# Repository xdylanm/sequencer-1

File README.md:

# Sequencer One

An open step sequencer platform.

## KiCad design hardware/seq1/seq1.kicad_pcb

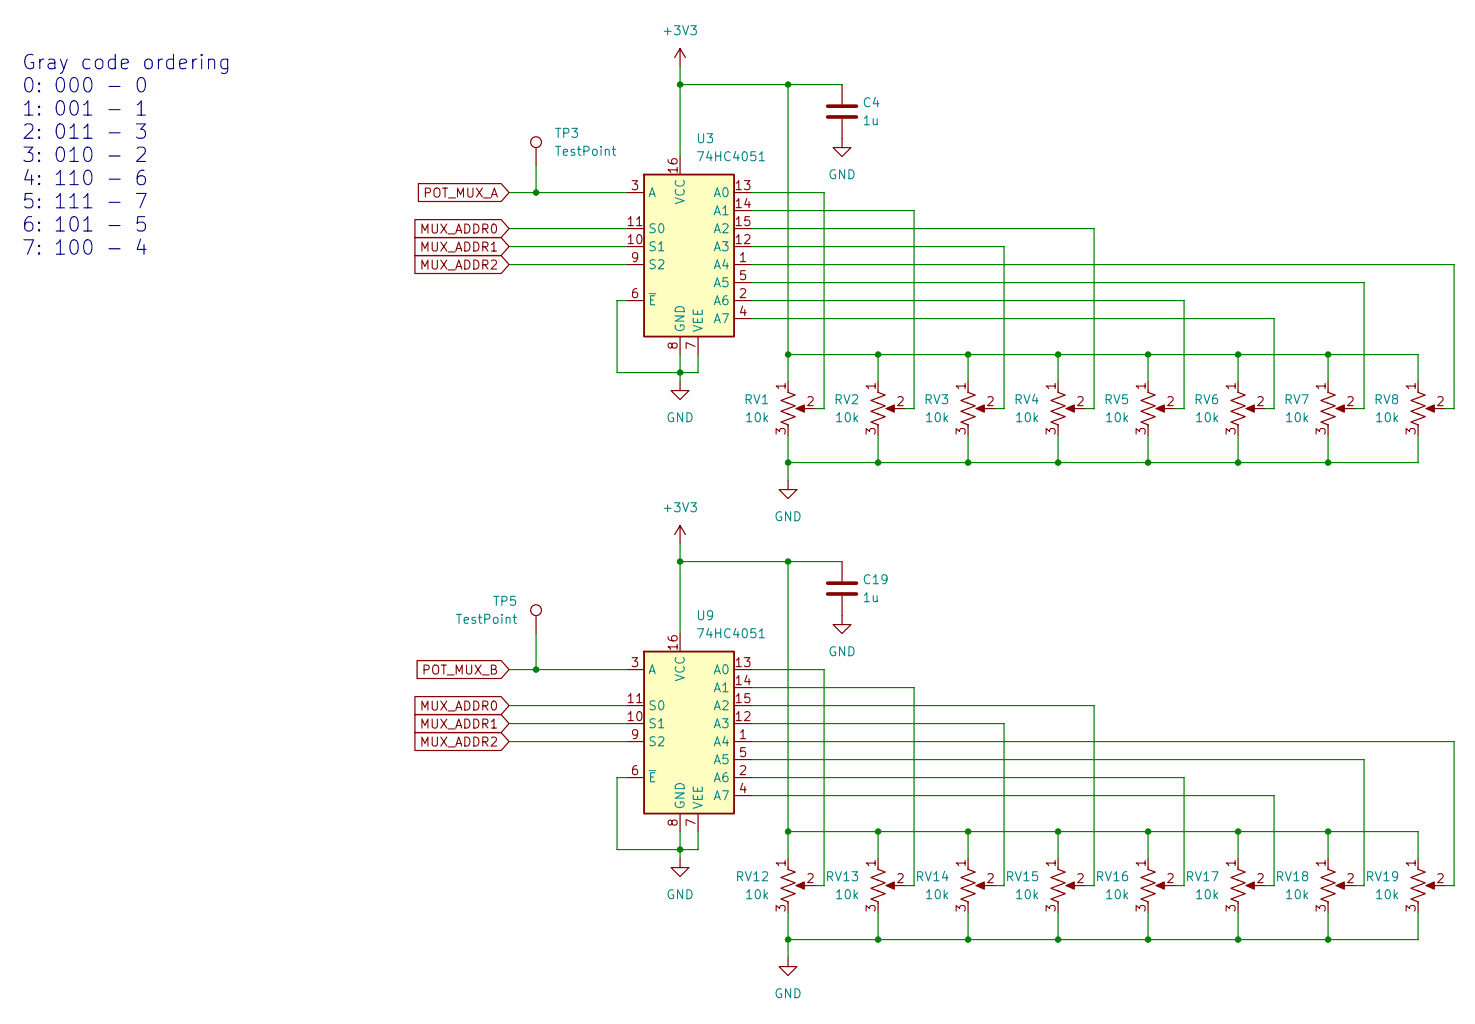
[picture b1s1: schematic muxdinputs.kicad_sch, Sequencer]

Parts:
C4, C19: 1u; C_Disc_D5.0mm_W2.5mm_P2.50mm
RV1, RV2, RV3, RV4, RV5, RV6, RV7, RV8, RV12, RV13, RV14, RV15, RV16, RV17, RV18, RV19: 10k; Potentiometer_Bourns_PTV09A-1_Single_Vertical
TP3, TP5: TestPoint; PinHeader_1x01_P2.54mm_Vertical
U3, U9: 74HC4051; DIP-16_W7.62mm_Socket

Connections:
+3V3: C4.1, C19.1, RV1.1, RV2.1, RV3.1, RV4.1, RV5.1, RV6.1, RV7.1, RV8.1, RV12.1, RV13.1, RV14.1, RV15.1, RV16.1, RV17.1, RV18.1, RV19.1, U3.16 (VCC), U9.16 (VCC); also elsewhere on the board
GND: C4.2, C19.2, RV1.3, RV2.3, RV3.3, RV4.3, RV5.3, RV6.3, RV7.3, RV8.3, RV12.3, RV13.3, RV14.3, RV15.3, RV16.3, RV17.3, RV18.3, RV19.3, U3.6 (~E), U3.7 (VEE), U3.8 (GND), U9.6 (~E), U9.7 (VEE), U9.8 (GND); also elsewhere on the board
MUX_ADDR0: U3.11 (S0), U9.11 (S0); also elsewhere on the board
MUX_ADDR1: U3.10 (S1), U9.10 (S1); also elsewhere on the board
MUX_ADDR2: U3.9 (S2), U9.9 (S2); also elsewhere on the board
unnamed: RV1.2, U3.13 (A0)
unnamed: RV2.2, U3.14 (A1)
unnamed: RV4.2, U3.15 (A2)
unnamed: RV3.2, U3.12 (A3)
unnamed: RV8.2, U3.1 (A4)
unnamed: RV7.2, U3.5 (A5)
unnamed: RV5.2, U3.2 (A6)
unnamed: RV6.2, U3.4 (A7)
unnamed: RV12.2, U9.13 (A0)
unnamed: RV13.2, U9.14 (A1)
unnamed: RV15.2, U9.15 (A2)
unnamed: RV14.2, U9.12 (A3)
unnamed: RV19.2, U9.1 (A4)
unnamed: RV18.2, U9.5 (A5)
unnamed: RV16.2, U9.2 (A6)
unnamed: RV17.2, U9.4 (A7)
POT_MUX_A: TP3.1, U3.3 (A); also elsewhere on the board
POT_MUX_B: TP5.1, U9.3 (A); also elsewhere on the board

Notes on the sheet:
Gray code ordering 0: 000 - 0 1: 001 - 1 2: 011 - 3 3: 010 - 2 4: 110 - 6 5: 111 - 7 6: 101 - 5 7: 100 - 4

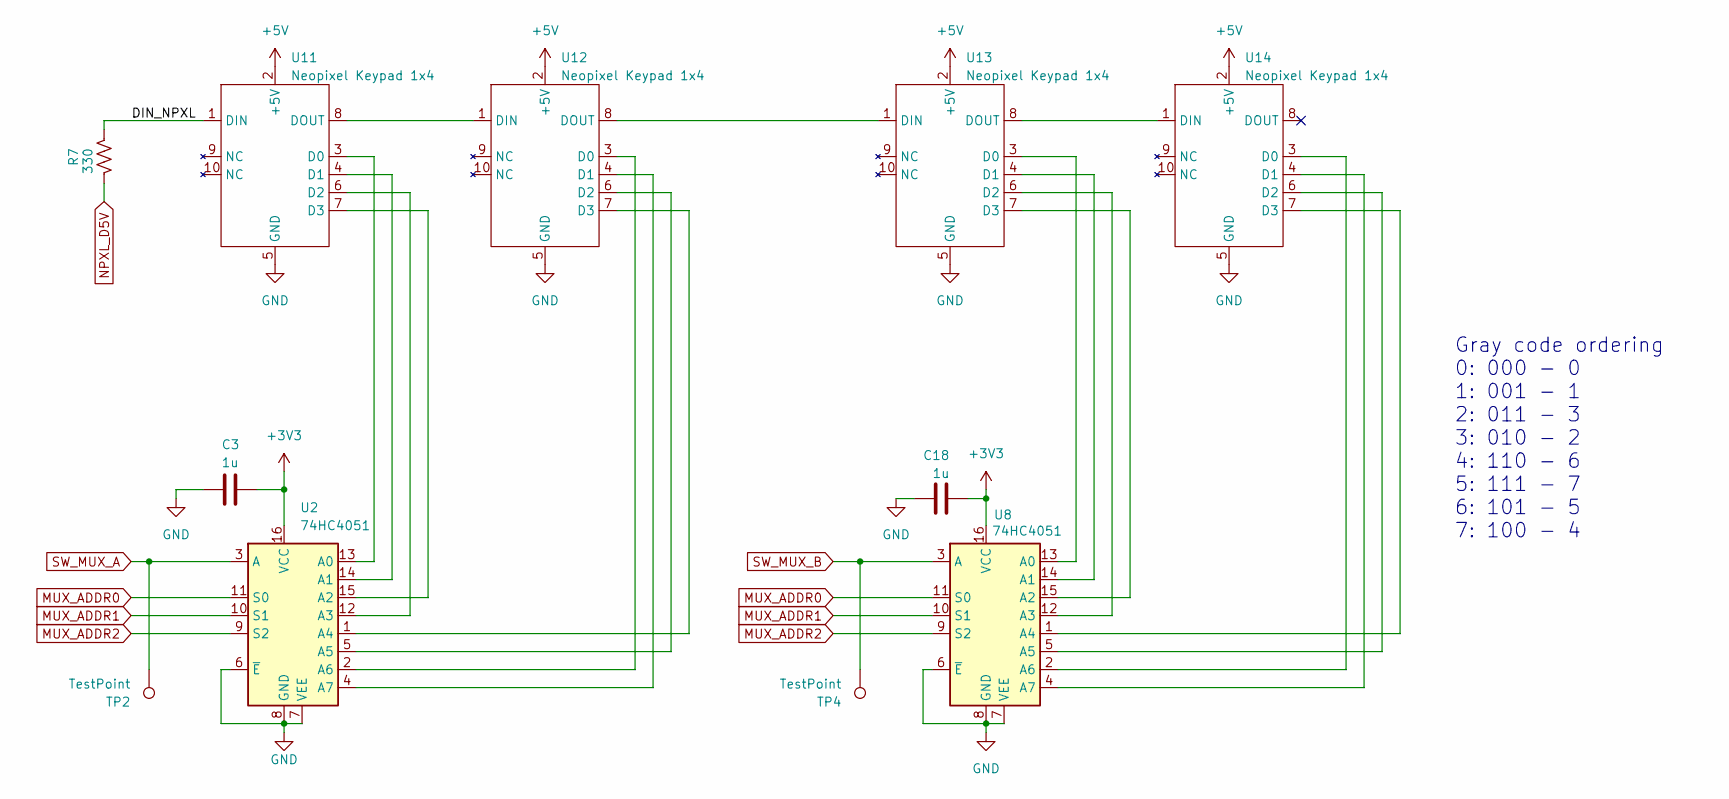
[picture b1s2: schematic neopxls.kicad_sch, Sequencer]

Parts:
C3, C18: 1u; C_Disc_D5.0mm_W2.5mm_P2.50mm
R7: 330; R_Axial_DIN0204_L3.6mm_D1.6mm_P2.54mm_Vertical
TP2, TP4: TestPoint; PinHeader_1x01_P2.54mm_Vertical
U2, U8: 74HC4051; DIP-16_W7.62mm_Socket
U11, U12, U13, U14: Neopixel Keypad 1x4; SW_Keypad_PushButton_1x4_Riser

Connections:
+3V3: C3.1, C18.2, U2.16 (VCC), U8.16 (VCC); also elsewhere on the board
+5V: U11.2 (+5V), U12.2 (+5V), U13.2 (+5V), U14.2 (+5V); also elsewhere on the board
/neopxls/DIN_NPXL: R7.2, U11.1 (DIN)
GND: C3.2, C18.1, U2.6 (~E), U2.7 (VEE), U2.8 (GND), U8.6 (~E), U8.7 (VEE), U8.8 (GND), U11.5 (GND), U12.5 (GND), U13.5 (GND), U14.5 (GND); also elsewhere on the board
MUX_ADDR0: U2.11 (S0), U8.11 (S0); also elsewhere on the board
MUX_ADDR1: U2.10 (S1), U8.10 (S1); also elsewhere on the board
MUX_ADDR2: U2.9 (S2), U8.9 (S2); also elsewhere on the board
NPXL_D5V: R7.1; also elsewhere on the board
unnamed: U2.13 (A0), U11.3 (D0)
unnamed: U2.14 (A1), U11.4 (D1)
unnamed: U2.12 (A3), U11.6 (D2)
unnamed: U2.15 (A2), U11.7 (D3)
unnamed: U11.8 (DOUT), U12.1 (DIN)
unnamed: U2.2 (A6), U12.3 (D0)
unnamed: U2.4 (A7), U12.4 (D1)
unnamed: U2.5 (A5), U12.6 (D2)
unnamed: U2.1 (A4), U12.7 (D3)
unnamed: U12.8 (DOUT), U13.1 (DIN)
unnamed: U8.13 (A0), U13.3 (D0)
unnamed: U8.14 (A1), U13.4 (D1)
unnamed: U8.12 (A3), U13.6 (D2)
unnamed: U8.15 (A2), U13.7 (D3)
unnamed: U13.8 (DOUT), U14.1 (DIN)
unnamed: U8.2 (A6), U14.3 (D0)
unnamed: U8.4 (A7), U14.4 (D1)
unnamed: U8.5 (A5), U14.6 (D2)
unnamed: U8.1 (A4), U14.7 (D3)
SW_MUX_A: TP2.1, U2.3 (A); also elsewhere on the board
SW_MUX_B: TP4.1, U8.3 (A); also elsewhere on the board

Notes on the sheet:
Gray code ordering 0: 000 - 0 1: 001 - 1 2: 011 - 3 3: 010 - 2 4: 110 - 6 5: 111 - 7 6: 101 - 5 7: 100 - 4

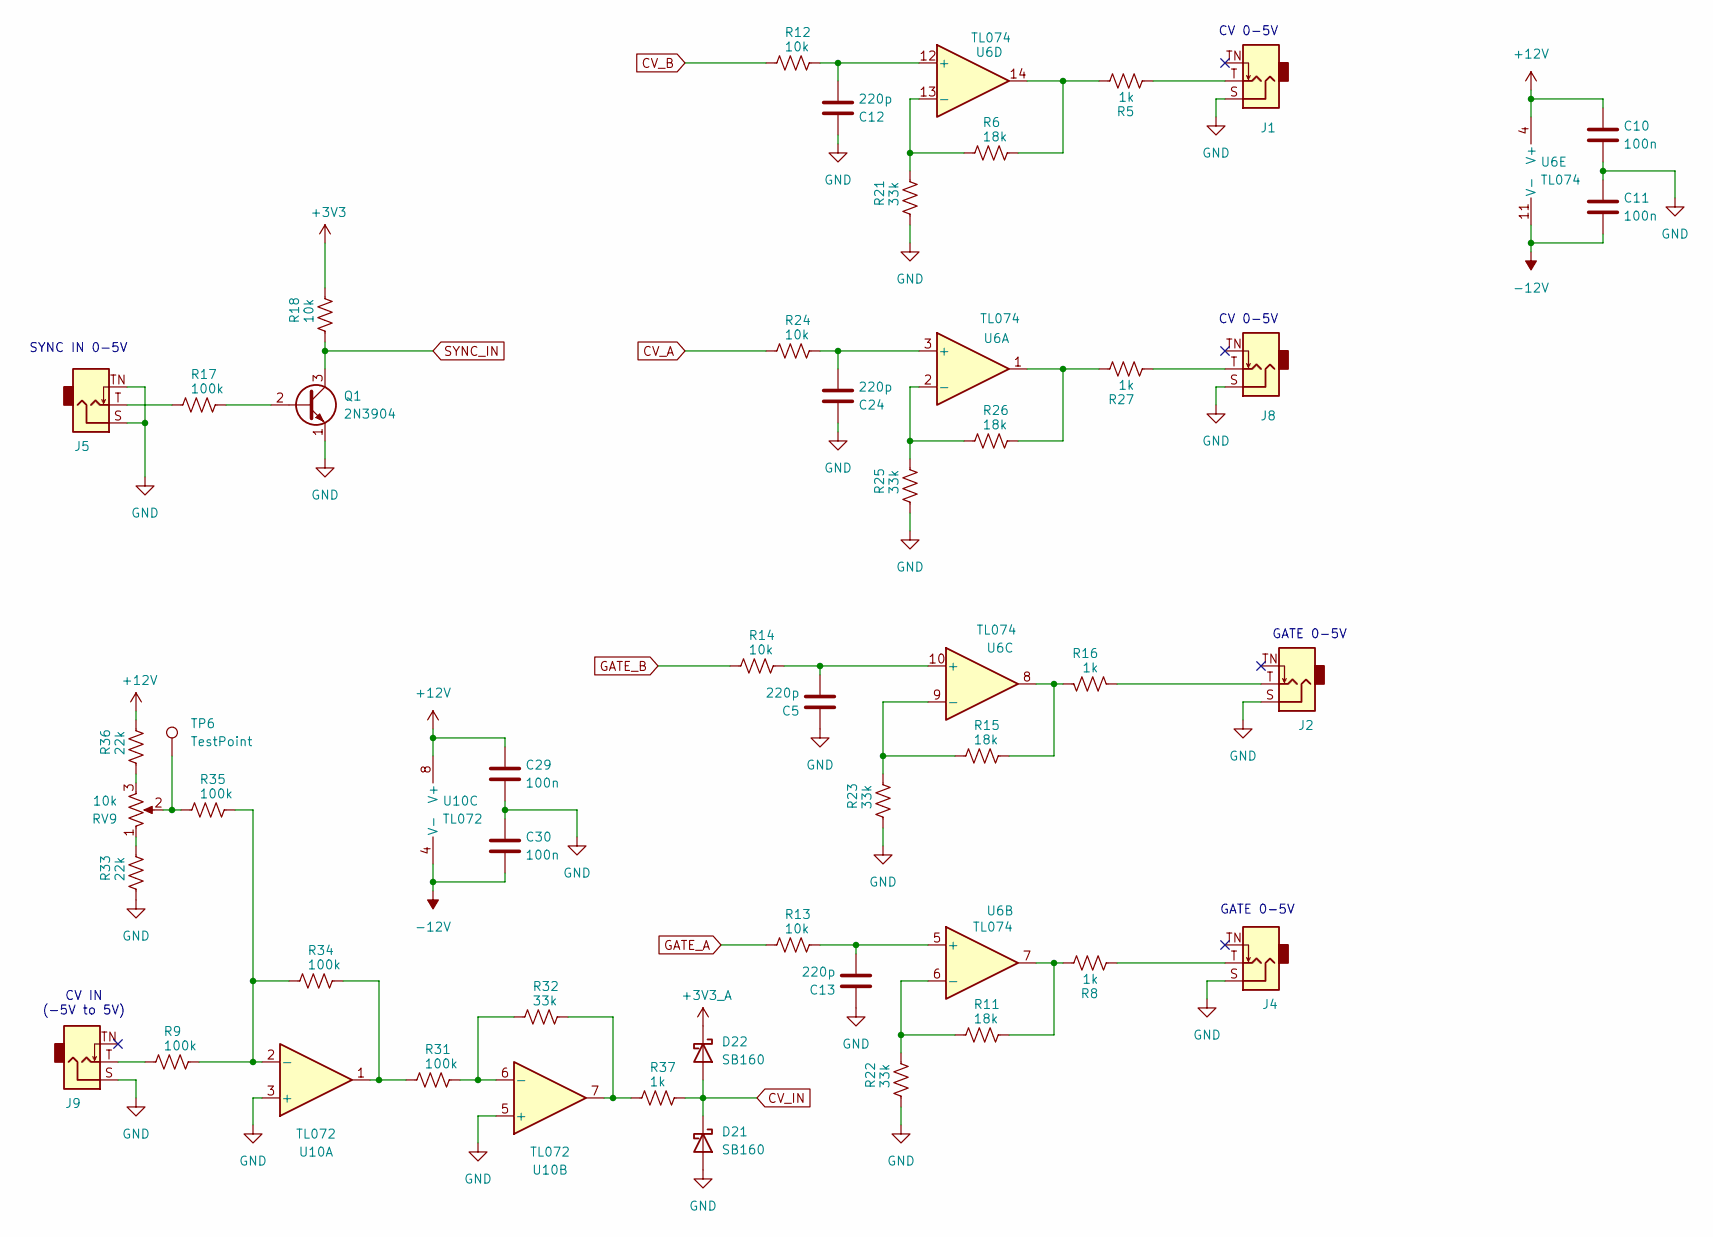
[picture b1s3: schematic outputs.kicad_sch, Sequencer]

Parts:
C5, C12, C13, C24: 220p; C_Disc_D5.0mm_W2.5mm_P2.50mm
C10, C11, C29, C30: 100n; C_Disc_D5.0mm_W2.5mm_P2.50mm
D21, D22: SB160; D_DO-35_SOD27_P2.54mm_Vertical_AnodeUp
J1, J2, J4, J5, J8, J9: AudioJack2_SwitchT; Jack_3.5mm_QingPu_WQP-PJ301M-12_Vertical
Q1: 2N3904; TO-92_Inline_Wide
R5, R8, R16, R37: 1k; R_Axial_DIN0204_L3.6mm_D1.6mm_P2.54mm_Vertical
R6, R11, R15, R26: 18k; R_Axial_DIN0204_L3.6mm_D1.6mm_P2.54mm_Vertical
R9, R17, R34, R35: 100k; R_Axial_DIN0204_L3.6mm_D1.6mm_P2.54mm_Vertical
R12, R18, R24: 10k; R_Axial_DIN0204_L3.6mm_D1.6mm_P2.54mm_Vertical
R13, R14: 10k; R_Axial_DIN0207_L6.3mm_D2.5mm_P10.16mm_Horizontal
R21, R22, R23, R25, R32: 33k; R_Axial_DIN0204_L3.6mm_D1.6mm_P2.54mm_Vertical
R27: 1k; R_Axial_DIN0204_L3.6mm_D1.6mm_P7.62mm_Horizontal
R31: 100k; R_Axial_DIN0204_L3.6mm_D1.6mm_P7.62mm_Horizontal
R33, R36: 22k; R_Axial_DIN0204_L3.6mm_D1.6mm_P2.54mm_Vertical
RV9: 10k; Potentiometer_Piher_PT-6-V_Vertical
TP6: TestPoint; PinHeader_1x01_P2.54mm_Vertical
U6: TL074; DIP-14_W7.62mm_Socket
U10: TL072; DIP-8_W7.62mm_Socket

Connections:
+3V3: R18.1; also elsewhere on the board
+3V3_A: D22.1 (K); also elsewhere on the board
+12V: C10.1, C29.1, R36.1, U6.4 (V+), U10.8 (V+); also elsewhere on the board
-12V: C11.2, C30.2, U6.11 (V-), U10.4 (V-); also elsewhere on the board
CV_A: R24.2; also elsewhere on the board
CV_B: R12.2; also elsewhere on the board
CV_IN: D21.1 (K), D22.2 (A), R37.1; also elsewhere on the board
GATE_A: R13.2; also elsewhere on the board
GATE_B: R14.2; also elsewhere on the board
GND: C5.1, C10.2, C11.1, C12.1, C13.1, C24.1, C29.2, C30.1, D21.2 (A), J1.S, J2.S, J4.S, J5.S, J5.TN, J8.S, J9.S, Q1.1 (E), R21.2, R22.2, R23.2, R25.2, R33.2, U10.3 (+), U10.5 (+); also elsewhere on the board
unnamed: J1.T, R5.2
unnamed: J2.T, R16.2
unnamed: J4.T, R8.2
unnamed: J5.T, R17.2
unnamed: J8.T, R27.2
unnamed: J9.T, R9.2
unnamed: Q1.2 (B), R17.1
unnamed: R5.1, R6.1, U6.14
unnamed: R8.1, R11.1, U6.7
unnamed: R15.1, R16.1, U6.8
unnamed: R26.1, R27.1, U6.1
unnamed: R31.2, R34.1, U10.1
unnamed: R32.1, R37.2, U10.7
unnamed: R33.1, RV9.1
unnamed: R35.2, RV9.2, TP6.1
unnamed: R36.2, RV9.3
unnamed: C24.2, R24.1, U6.3 (+)
unnamed: R25.1, R26.2, U6.2 (-)
unnamed: C13.2, R13.1, U6.5 (+)
unnamed: R11.2, R22.1, U6.6 (-)
unnamed: C5.2, R14.1, U6.10 (+)
unnamed: R15.2, R23.1, U6.9 (-)
unnamed: C12.2, R12.1, U6.12 (+)
unnamed: R6.2, R21.1, U6.13 (-)
unnamed: R9.1, R34.2, R35.1, U10.2 (-)
unnamed: R31.1, R32.2, U10.6 (-)
SYNC_IN: Q1.3 (C), R18.2; also elsewhere on the board

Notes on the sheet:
SYNC IN 0-5V
CV IN (-5V to 5V)
GATE 0-5V
CV 0-5V

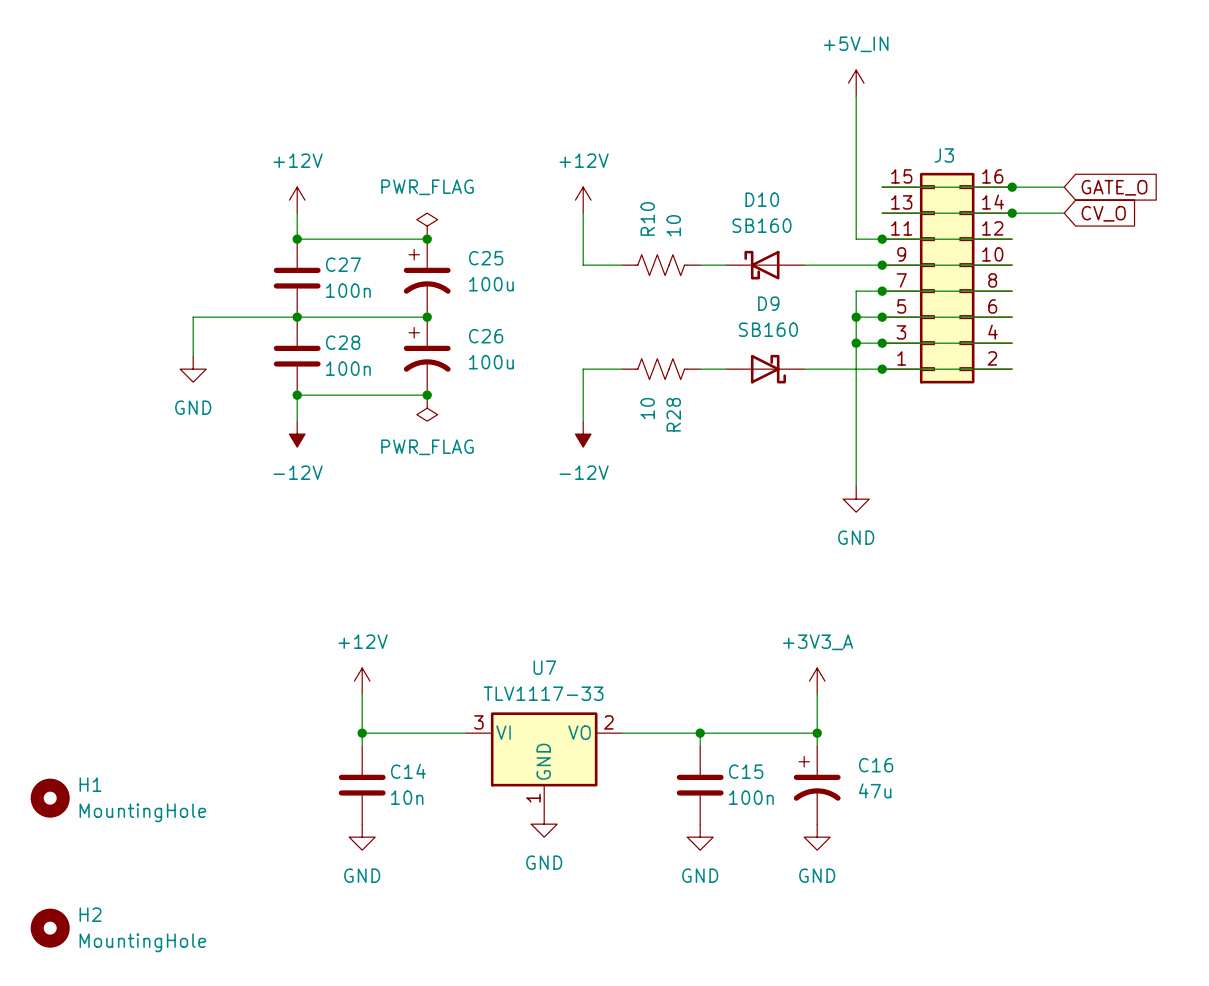
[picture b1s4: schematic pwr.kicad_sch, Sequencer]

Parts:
C14: 10n; C_Disc_D5.0mm_W2.5mm_P2.50mm
C15, C27, C28: 100n; C_Disc_D5.0mm_W2.5mm_P2.50mm
C16: 47u; CP_Radial_D5.0mm_P2.50mm
C25, C26: 100u; CP_Radial_D6.3mm_P2.50mm
D9, D10: SB160; D_DO-35_SOD27_P2.54mm_Vertical_AnodeUp
H1, H2: MountingHole; MountingHole_3.2mm_M3_DIN965
J3: Conn_02x08_Odd_Even; IDC-Header_2x08_P2.54mm_Vertical
R10: 10; R_Axial_DIN0204_L3.6mm_D1.6mm_P2.54mm_Vertical
R28: 10; R_Axial_DIN0207_L6.3mm_D2.5mm_P7.62mm_Horizontal
U7: TLV1117-33; SOT-223-3_TabPin2

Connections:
+3V3_A: C15.1, C16.1, U7.2 (VO); also elsewhere on the board
+5V_IN: J3.11, J3.12; also elsewhere on the board
+12V: C14.1, C25.1, C27.1, R10.1, U7.3 (VI); also elsewhere on the board
-12V: C26.2, C28.2, R28.2; also elsewhere on the board
CV_O: J3.13, J3.14
GATE_O: J3.15, J3.16
GND: C14.2, C15.2, C16.2, C25.2, C26.1, C27.2, C28.1, J3.3, J3.4, J3.5, J3.6, J3.7, J3.8, U7.1 (GND); also elsewhere on the board
unnamed: D9.2 (A), R28.1
unnamed: D9.1 (K), J3.1, J3.2
unnamed: D10.2 (A), J3.9, J3.10
unnamed: D10.1 (K), R10.2

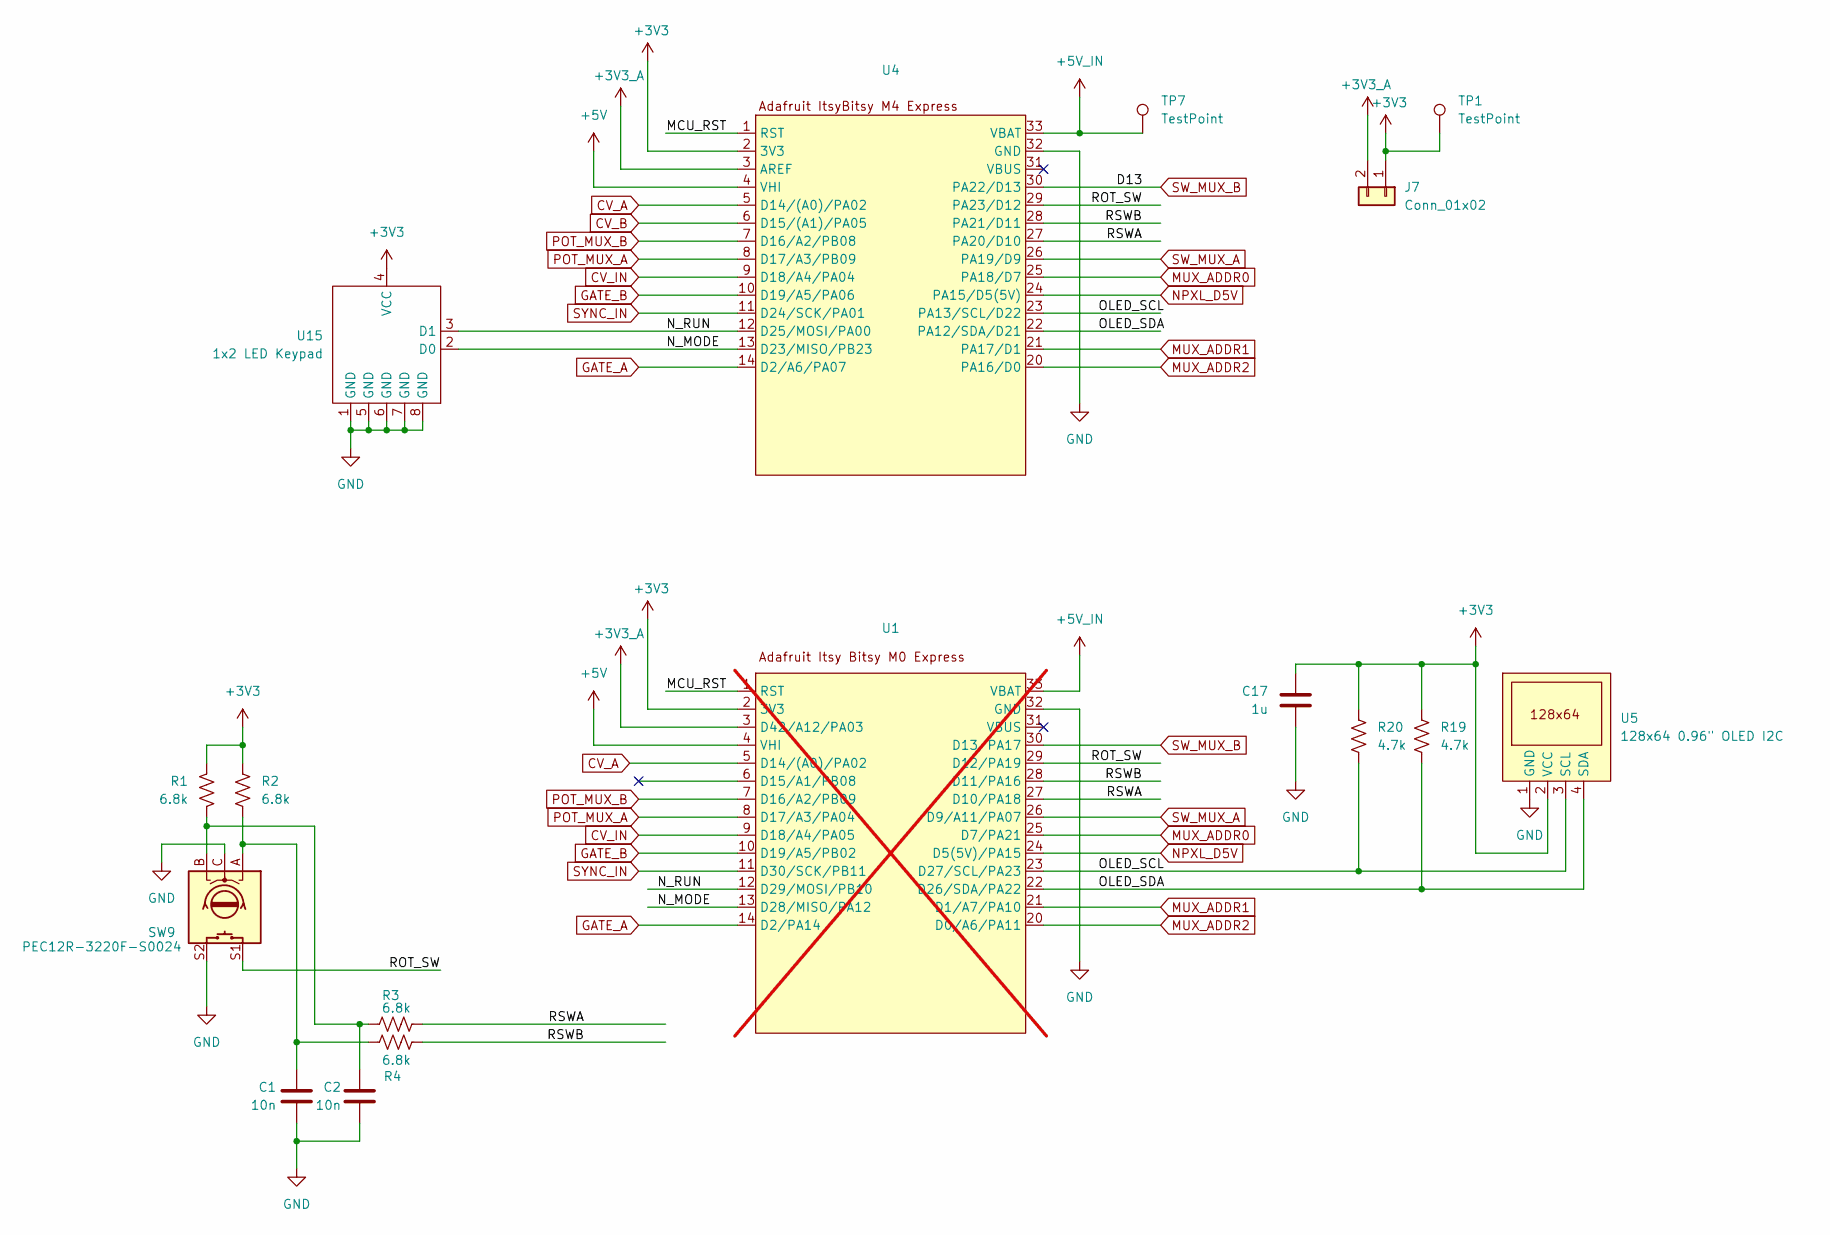
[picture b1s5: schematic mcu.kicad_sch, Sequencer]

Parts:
C1, C2: 10n; C_Disc_D5.0mm_W2.5mm_P2.50mm
C17: 1u; C_Disc_D5.0mm_W2.5mm_P2.50mm
J7: Conn_01x02; PinHeader_1x02_P2.54mm_Vertical
R1, R2, R3, R4: 6.8k; R_Axial_DIN0204_L3.6mm_D1.6mm_P2.54mm_Vertical
R19, R20: 4.7k; R_Axial_DIN0204_L3.6mm_D1.6mm_P2.54mm_Vertical
SW9: PEC12R-3220F-S0024; RotaryEncoder_Bourns_Vertical_PEC12R-3x17F-Sxxxx
TP1, TP7: TestPoint; PinHeader_1x01_P2.54mm_Vertical
U1: Adafruit_ItsyBitsy_M0_Express_DIP; not fitted
U4: Adafruit_ItsyBitsy_M0_Express_DIP
U5: 128x64 0.96" OLED I2C; OLED_0.96in_SSD1306_I2C
U15: 1x2 LED Keypad; SW_Keypad_PushButton_1x2_Riser

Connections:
+3V3: C17.1, J7.1, R1.1, R2.1, R19.1, R20.1, TP1.1, U1.2 (3V3), U4.2 (3V3), U5.2 (VCC), U15.4 (VCC); also elsewhere on the board
+3V3_A: J7.2, U1.3 (D42/A12/PA03), U4.3 (AREF); also elsewhere on the board
+5V: U1.4 (VHI), U4.4 (VHI); also elsewhere on the board
+5V_IN: TP7.1, U1.33 (VBAT), U4.33 (VBAT); also elsewhere on the board
/mcu/MCU_RST: U1.1 (RST), U4.1 (RST)
/mcu/N_MODE: U1.13 (D28/MISO/PA12), U4.13 (D23/MISO/PB23), U15.2 (D0)
/mcu/N_RUN: U1.12 (D29/MOSI/PB10), U4.12 (D25/MOSI/PA00), U15.3 (D1)
/mcu/OLED_SCL: R20.2, U1.23 (D27/SCL/PA23), U4.23 (PA13/SCL/D22), U5.3 (SCL)
/mcu/OLED_SDA: R19.2, U1.22 (D26/SDA/PA22), U4.22 (PA12/SDA/D21), U5.4 (SDA)
/mcu/ROT_SW: SW9.S1, U1.29 (D12/PA19), U4.29 (PA23/D12)
/mcu/RSWA: R3.1, U1.27 (D10/PA18), U4.27 (PA20/D10)
/mcu/RSWB: R4.1, U1.28 (D11/PA16), U4.28 (PA21/D11)
CV_A: U1.5 (D14/(A0)/PA02), U4.5 (D14/(A0)/PA02); also elsewhere on the board
CV_B: U4.6 (D15/(A1)/PA05); also elsewhere on the board
CV_IN: U1.9 (D18/A4/PA05), U4.9 (D18/A4/PA04); also elsewhere on the board
GATE_A: U1.14 (D2/PA14), U4.14 (D2/A6/PA07); also elsewhere on the board
GATE_B: U1.10 (D19/A5/PB02), U4.10 (D19/A5/PA06); also elsewhere on the board
GND: C1.2, C2.2, C17.2, SW9.C, SW9.S2, U1.32 (GND), U4.32 (GND), U5.1 (GND), U15.1 (GND), U15.5 (GND), U15.6 (GND), U15.7 (GND), U15.8 (GND); also elsewhere on the board
MUX_ADDR0: U1.25 (D7/PA21), U4.25 (PA18/D7); also elsewhere on the board
MUX_ADDR1: U1.21 (D1/A7/PA10), U4.21 (PA17/D1); also elsewhere on the board
MUX_ADDR2: U1.20 (D0/A6/PA11), U4.20 (PA16/D0); also elsewhere on the board
NPXL_D5V: U1.24 (D5(5V)/PA15), U4.24 (PA15/D5(5V)); also elsewhere on the board
unnamed: C1.1, R2.2, R4.2, SW9.A
unnamed: C2.1, R1.2, R3.2, SW9.B
POT_MUX_A: U1.8 (D17/A3/PA04), U4.8 (D17/A3/PB09); also elsewhere on the board
POT_MUX_B: U1.7 (D16/A2/PB09), U4.7 (D16/A2/PB08); also elsewhere on the board
SW_MUX_A: U1.26 (D9/A11/PA07), U4.26 (PA19/D9); also elsewhere on the board
SW_MUX_B: U1.30 (D13/PA17), U4.30 (PA22/D13); also elsewhere on the board
SYNC_IN: U1.11 (D30/SCK/PB11), U4.11 (D24/SCK/PA01); also elsewhere on the board

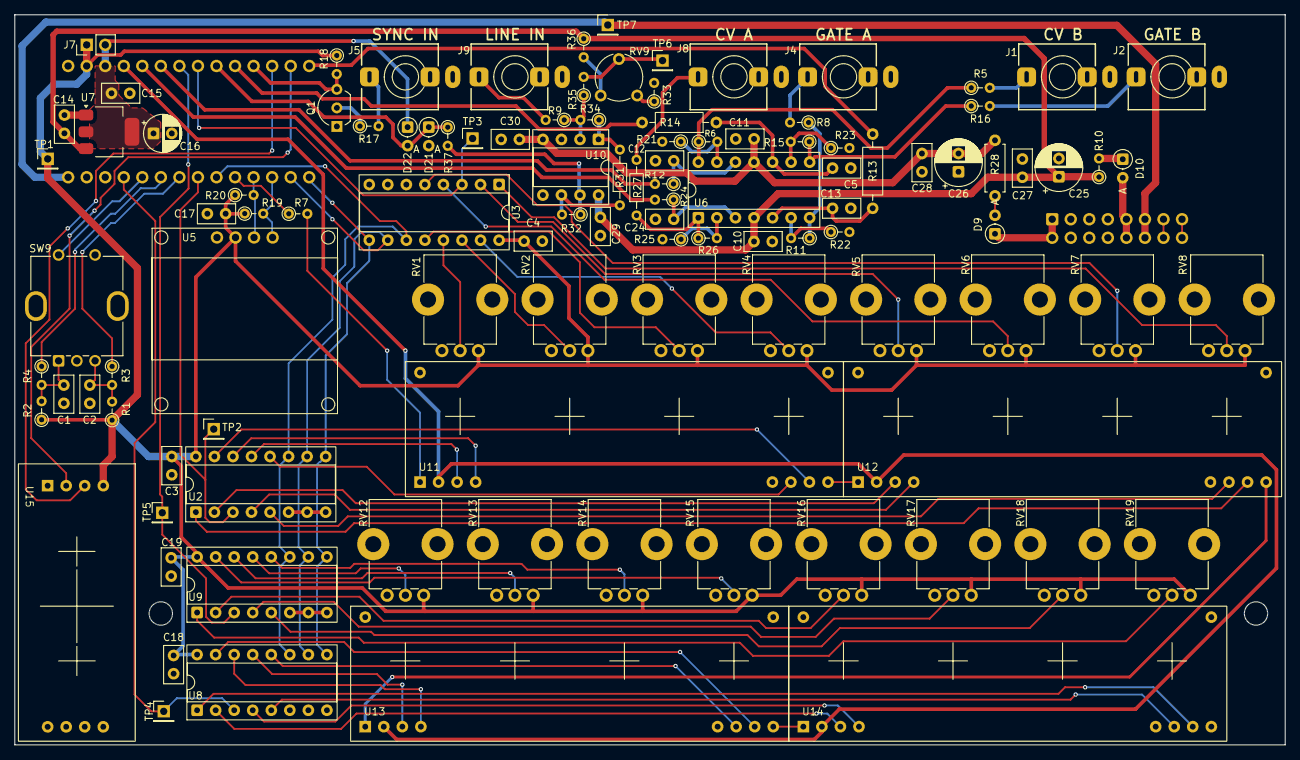
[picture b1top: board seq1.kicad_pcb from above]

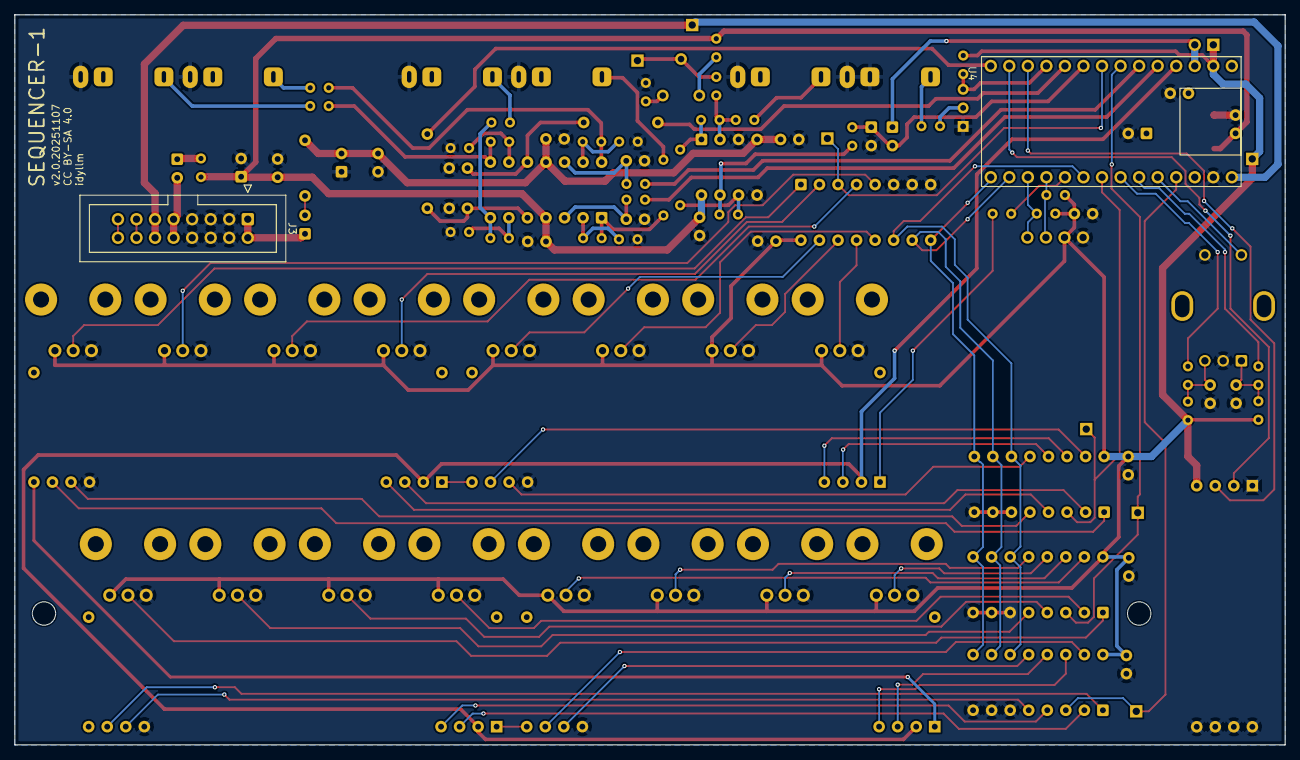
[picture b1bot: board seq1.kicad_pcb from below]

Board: 2 copper layers, 174.0 x 100.0 mm, 111 parts (2 on the bottom side), 98 nets.

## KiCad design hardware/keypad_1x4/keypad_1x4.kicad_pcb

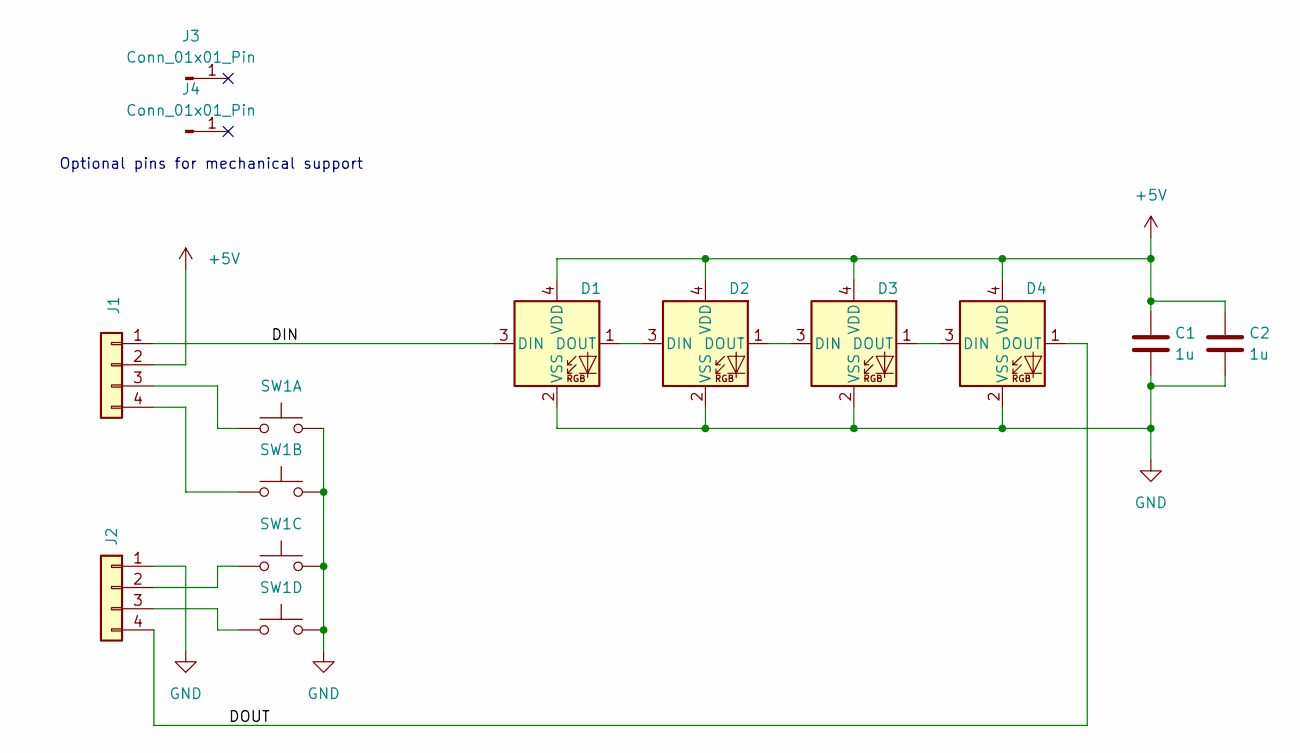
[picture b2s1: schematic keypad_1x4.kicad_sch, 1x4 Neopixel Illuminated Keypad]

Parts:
C1, C2: 1u; C_Disc_D5.0mm_W2.5mm_P5.00mm
D1, D2, D3, D4: SK6805; LED_SK6805_PLCC4_2.4x2.7mm_P1.3mm
J1, J2: Conn_01x04; PinHeader_1x04_P2.54mm_Vertical
J3, J4: Conn_01x01_Pin; PinHeader_1x01_P2.54mm_Vertical
SW1: SW_Push_x4; SW_Silicone_Keypad_PushButton_10mm_4x1grid_NH

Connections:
+5V: C1.1, C2.1, D1.4 (VDD), D2.4 (VDD), D3.4 (VDD), D4.4 (VDD), J1.2
/DIN: D1.3 (DIN), J1.1
/DOUT: D4.1 (DOUT), J2.4
GND: C1.2, C2.2, D1.2 (VSS), D2.2 (VSS), D3.2 (VSS), D4.2 (VSS), J2.1, SW1.1, SW1.3, SW1.5, SW1.7
unnamed: D1.1 (DOUT), D2.3 (DIN)
unnamed: D2.1 (DOUT), D3.3 (DIN)
unnamed: D3.1 (DOUT), D4.3 (DIN)
unnamed: J1.3, SW1.2
unnamed: J1.4, SW1.4
unnamed: J2.2, SW1.6
unnamed: J2.3, SW1.8

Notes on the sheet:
Optional pins for mechanical support

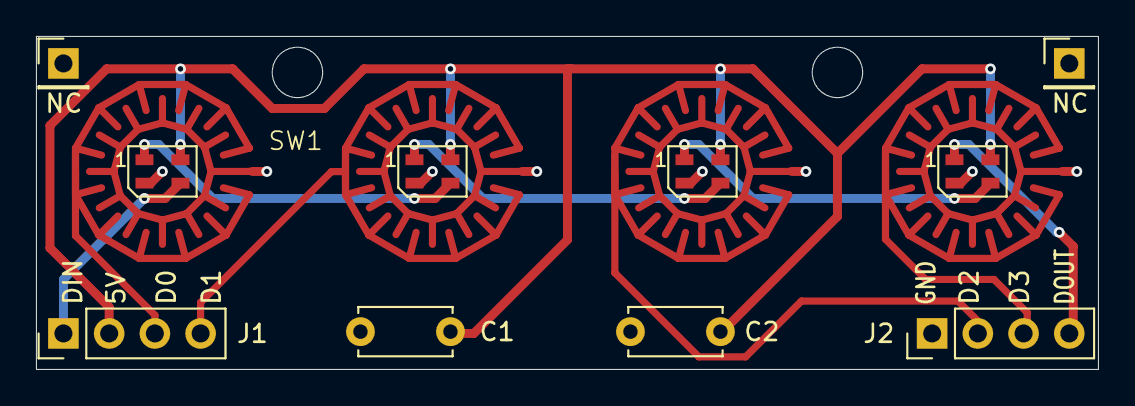
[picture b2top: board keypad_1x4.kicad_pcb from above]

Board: 2 copper layers, 59.0 x 18.5 mm, 11 parts (0 on the bottom side), 11 nets.

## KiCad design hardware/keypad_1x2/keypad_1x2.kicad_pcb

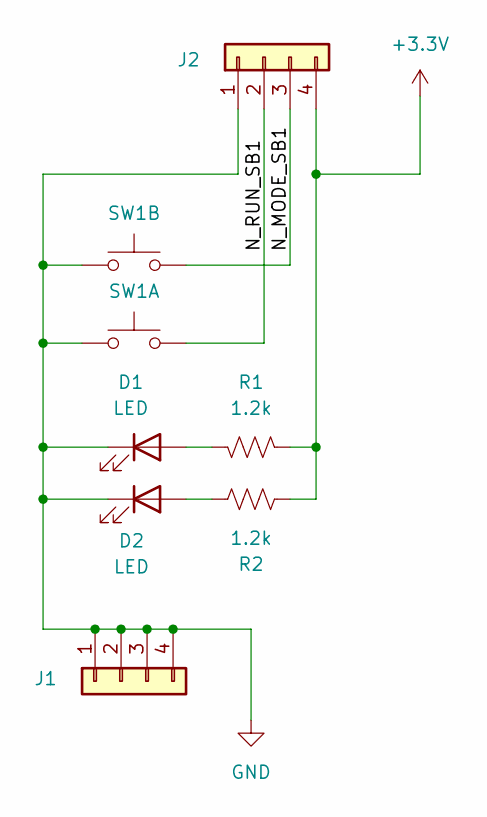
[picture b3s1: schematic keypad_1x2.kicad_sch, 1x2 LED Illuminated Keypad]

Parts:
D1, D2: LED; LED_3mm_Backside_SMD
J1, J2: Conn_01x04; PinHeader_1x04_P2.54mm_Vertical
R1, R2: 1.2k; R_Axial_DIN0204_L3.6mm_D1.6mm_P2.54mm_Vertical
SW1: SW_Push_x2; SW_Silicone_Keypad_PushButton_10mm_2x1grid_NH

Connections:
+3.3V: J2.4, R1.2, R2.2
/N_MODE_SB1: J2.3, SW1.4
/N_RUN_SB1: J2.2, SW1.2
GND: D1.1 (K), D2.1 (K), J1.1, J1.2, J1.3, J1.4, J2.1, SW1.1, SW1.3
unnamed: D1.2 (A), R1.1
unnamed: D2.2 (A), R2.1

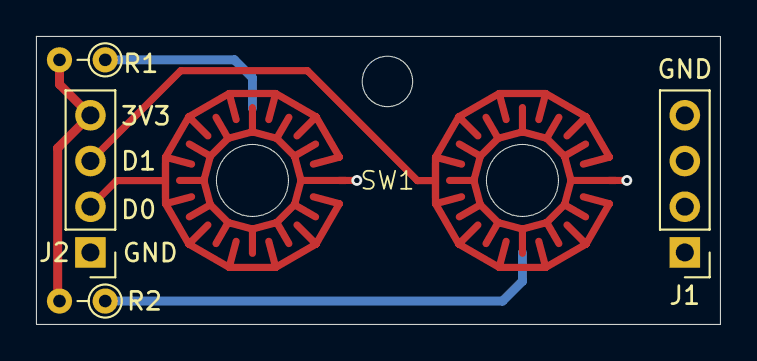
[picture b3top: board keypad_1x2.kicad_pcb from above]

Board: 2 copper layers, 38.0 x 16.0 mm, 7 parts (0 on the bottom side), 6 nets.

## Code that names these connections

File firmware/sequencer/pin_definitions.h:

#pragma once

#include <Arduino.h>
/*!
  \file pin_definitions.h

  \brief Labels for physical pins

  To support different boards (QT Py & Itsy Bitsy variants), different 
  pin assignments are required. Not all capabilities are available on
  all boards. 

  Defines starting with `PIN_` refer to "Arduino" pin numbers (board-dependent).

  Defines starting with `PAX_` refer to the IO pin number from the IO
  multiplexing table in the SAMD datasheets (when the pin is not broken out to
  a header on the board or when required to configure the peripheral).
  
*/

// Pin definitions
//  + PIN_ prefix for Arduino numbering
//  + PAX_ prefix for SAMD21 IO pin numbering (e.g. SAMD PA02 = Arduino A0/D0 on the QtPY) 

////////////////////// QT Py /////////////////////////////////////
#if defined(ADAFRUIT_QTPY_M0)

#define PIN_CV_DAC_OUT 0
// pin 1 is POT_MUX (PA03)
#define PIN_RUN_STOP_BUTTON 2
#define PIN_MODE_BUTTON 3
// pin 4 & 5 (SDA & SCL) for the display I2C
#define PIN_ROT_SW 6
#define PIN_GATE_OUT 7
#define PIN_ROT_IN1 8
#define PIN_ROT_IN2 9
#define PIN_STATUS_NEOPIXELS 10 // must be MOSI for DMA 

// pin definitions for ADC found in adc_config

// QTPy needs to use pins from Flash interface
#define PAX_MUXD_STEP_BUTTON 8  // FLASH_CS with 5k1 pullup
#define PAX_MUX_ADDR0 19
#define PAX_MUX_ADDR1 22
#define PAX_MUX_ADDR2 23

//////////////// ITSY BITSY M4 (SAMD51) ///////////////////////
#elif defined(ADAFRUIT_ITSYBITSY_M4_EXPRESS)

#define PIN_CV_DAC_OUT PIN_DAC0  // A0/D14
// pin D15-D17 are not used
// pin D18 is POT_MUX (PA04)
#define PIN_SYNC_IN 19
#define PIN_SYNC_OUT 24

#define PIN_MODE_BUTTON 23
#define PIN_RUN_STOP_BUTTON 25

#define PIN_GATE_OUT 2

// pin D3 and D4 are not used

#define PIN_MUX_ADDR0 0
#define PIN_MUX_ADDR1 1
#define PIN_MUX_ADDR2 7
// pin 21 & 22 (SDA & SCL) for the display I2C

#define PIN_STATUS_NEOPIXELS 5 // DMA capable with a built-in 5V level shifter

#define PIN_MUXD_STEP_BUTTON 9

#define PIN_ROT_IN1 10
#define PIN_ROT_IN2 11

#define PIN_ROT_SW 12

// D13 is not used -- built-in LED

// pin definitions for ADC found in adc_config, different for M0 & M4

////////////////////// Undefined /////////////////////////////////
#else
#error Unsupported board, pins not defined
#endif

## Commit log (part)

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2023-09-20 initial prototype firmware for i2c OLED display and rotary encoder
2024-03-18 initial design files
2024-03-18 adding initial rev of schematic
2024-03-22 firmware draft for sequencer, tested buttons and pots through the muxes, verified ADC config
2024-03-22 clean up timing diagram files
2024-03-22 initialized controller and run full tick loop. Added neopixel states in MachineState and tested run/stop behaviour with active/enable mode settings
2024-03-24 updates to schematic/layout (started layout). Added glyph and display class to manage and show status (PoC)
2024-04-08 menu system and adjustment through the physical interface
2024-04-08 Updates to menu and controller refactoring into machine state, added display for mode select state (issue #3)
2024-04-08 added level display on main canvas
2024-04-15 schematic and layout for v1 board
2024-04-15 layout clean up
2024-05-05 v1 board
2024-07-06 Adding support for the Itsy Bitsy M4 (SAMD51) architecture. Removed _util code and refactored to use the SAMD Utilities Library (SAMD_Utils.h). Compiles for QT Py M0, Itsy Bitsy M0 and M4
2024-07-07 fixing bugs in pin definitions
2024-07-07 bug in layout: order of pots reversed. Fixes for slide algo in controller, pin definitions and other fixes found in testing
2024-10-15 updating the board with new line in
2025-11-07 layout for v2 board (WIP) with risers part of same schematic/PBC
2025-11-07 moved 1x4 keypad to separate project
2025-11-07 Adding 1x2 LED illuminated keypad, updates to 1x4 board for gbrs
2025-11-07 tweaks to PCB layout from grb review
2025-11-07 updated schematic title blocks for v2, generated gerbers
2025-12-05 Updated docs for mkdocs conversion (WIP)
2025-12-06 Added a test for the neopixel 1x4 keypad breakout (using QtPy M0)

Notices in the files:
hardware/keypad_1x2/keypad_1x2.kicad_pcb:
CC BY-SA 4.0
idyllm CC BY-SA 4.0
